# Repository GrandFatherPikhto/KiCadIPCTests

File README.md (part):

# KiCad IPC Test Framework

**General purpose of the project** – creating a unified, safe, and extensible system for testing and automating interaction with the **KiCad** PCB editor via IPC (the `kipy` library). The toolkit allows you to:

- perform **smoke, safe, and mutating tests** on a real board;
- conduct **static contract analysis** of the installed version of `kipy`;
- automate typical operations (moving, flipping components, creating vias);
- diagnose connection state and reproduce known KiCad bugs.

The project is built around a **single runner** that manages configuration, logging, the test registry, and the connection to KiCad, ensuring integrity and repeatability of runs.

---

## Installation and Dependencies

- **Python 3.8+**
- **KiCad 9 or 10** with GUI running (IPC works only with an open PCB editor)
- **`kipy` library** – official Python wrapper for KiCad IPC (installed separately, see [repository](https://gitlab.com/kicad/libraries/kipy))
- Optionally for CLI netlist export – **`kicad-cli`** (included in KiCad)

It is recommended to use a virtual environment:

```bash
python -m venv venv
source venv/bin/activate   # Windows: venv\Scripts\activate
pip install kipy
```

---

## Configuration

All settings are done via a **single YAML file**. Minimal structure:

```yaml
kicad:
  timeout_ms: 20000               # IPC call timeout (ms)

logging:
  console_level: INFO             # console log level
  file: logs/test.log             # log file path
  file_level: DEBUG               # file log level
  rotate_max_bytes: 5242880       # max size per file
  rotate_backups: 3               # number of rotations

boards:                           # parameter profiles for different boards
  10CL006:
    ref: "C5"                     # default refdes
    pad: "1"                      # pad number
    zone: "RA_DECAP_ZONE"         # zone name
    net: "GND"                    # net name
    extra:                        # additional parameters
      offset_mm: 1.2

suites:                           # test groups
  smoke:
    enabled: true
    tests:
      smoke_footprints:
        enabled: true
  mutating:
    enabled: false                # dangerous tests are disabled by default
    tests:
      mutating_flip_then_update_items:
        enabled: false
        dangerous: true
        params:
          ref: "Ctest"
```

Parameters from `boards` and `tests` are merged via `resolve_params` (test parameters have higher priority).

---

## Running

**Main command:**

```bash
python -m runner.run --config <config.yaml> [--board <profile>] [--suite <suite>] [--test <test>]
```

- `--config` – required, path to YAML config.
- `--board` – board profile name (substitutes `ref/pad/zone/net` parameters).
- `--suite` – run only the specified suite.
- `--test` – run a specific test (even if not described in config – it will execute with default parameters, **except dangerous ones** – they require explicit `enabled: true`).

**Examples:**

```bash
# All safe tests for board 10CL006
python -m runner.run --config config/10CL006.yaml --board 10CL006 --suite safe

# Single smoke test on component C5
python -m runner.run --config config/10CL006.yaml --board 10CL006 --test smoke_footprints

# Dangerous test (only if enabled in config)
python -m runner.run --config config/10CL006.yaml --test decap_create_one_via
```

After execution, the runner outputs a summary `[PASS]/[FAIL]` and an exit code: `0` – all passed, `1` – some errors, `2` – attempt to run a disabled dangerous test.

---

## Project Structure

```
project_root/
├── core_api/                     # Base abstraction layer over kipy
│   ├── board.py                  # Transactions, board metadata (size, layers)
│   ├── footprints.py             # Footprint search, read, modification, flip
│   ├── geometry.py               # MM constant, coordinate utilities
│   ├── kicad_client.py           # Connection, run_action, version
│   ├── nets.py                   # Nets (search by name, code map)
│   ├── pads.py                   # Pads (obtained via definition.items)
│   ├── project.py                # Project and schematic paths
│   ├── selection.py              # Description of selected items
│   ├── vias.py                   # Create/delete vias
│   ├── zones.py                  # Zones (search, outline points)
│   └── __init__.py
│
├── runner/                       # Unified launch system
│   ├── config_schema.py          # Dataclass models and YAML loading
│   ├── logging_setup.py          # Logging setup (console + rotating file)
│   ├── registry.py               # Test registry (@register decorator)
│   ├── run.py                    # Main script (parsing, discovery, execution)
│   ├── step_helper.py            # call_step – logging with timing
│   └── __init__.py
│
├── tests/
│   ├── decap_tools/              # Dangerous tests for capacitors and vias
│   │   ├── test_create_one_via.py      # Create/delete one via
│   │   ├── test_flip_one_cap.py        # Flip component (toggle)
│   │   ├── test_move_one_cap.py        # Shift component along X
│   │   ├── test_via_placer.py          # Automatic via placement with keepout
│   │   ├── geometry/
│   │   │   ├── boundary.py             # Ray–polygon intersection, normals
│   │   │   └── keepout.py              # Keepout zones, free point search
│   │   └── __init__.py
│   │
│   ├── mutating/                 # Regression dangerous tests
│   │   ├── test_flip_then_update_items.py      # Stale object after flip
│   │   ├── test_footprint_rotation_linkage.py  # Rotation and schematic link (#21655)
│   │   ├── test_pad_ownership_comparison.py    # Comparison of pad acquisition methods
│   │   ├── test_refill_zones_busy_repro.py     # Eternal busy reproduction
│   │   └── __init__.py
│   │
│   ├── safe/                    # Safe tests (read-only)
│   │   ├── test_board_info.py          # Board summary (get_info)
│   │   ├── test_cli_netlist.py         # Netlist export via kicad-cli
│   │   ├── test_connection_reuse.py    # Single connection reuse check
│   │   ├── test_footprints_probe.py    # Temporary busy diagnostics
│   │   ├── test_project.py             # Project and schematic paths
│   │   ├── cli_utils.py                # kicad-cli utilities (not a test)
│   │   └── __init__.py
│   │
│   ├── smoke/                   # Smoke tests for basic modules
│   │   ├── test_board.py               # commit_with_retry (empty transaction)
│   │   ├── test_footprints.py          # Footprint reading and bounding box
│   │   ├── test_kicad_client.py        # Version and board re-fetch
│   │   ├── test_nets.py                # Net search by name
│   │   ├── test_pads.py                # Footprint pad reading
│   │   ├── test_selection.py           # Selection description (no input)
│   │   ├── test_vias.py                # Create/delete via (no leftovers)
│   │   ├── test_zones.py               # Zone search and outline point
│   │   └── __init__.py
│   │
│   ├── static/                  # Static contract checks of kipy
│   │   ├── test_kipy_contract.py       # 12 API incompatibility checks
│   │   └── __init__.py
│   │
│   ├── toy/                     # Dummy tests for runner debugging
│   │   ├── dummy_tests.py              # dummy_ok, fail, raises, needs_params, dangerous
│   │   └── __init__.py
│   │
│   └── __init__.py
│
├── config/                      # (example) YAML configs for different boards
│   └── test_config.yaml
│
└── logs/                        # Log files (auto-created)
    └── test.log
```

---

## Important Notes

- **Dangerous tests** (flag `dangerous: true`) are **never run** without explicit `enabled: true` in the config – this protects against accidental board damage.
- **Single connection** – all tests in one run use the same connection, preventing socket leaks.
- **After GUI flip**, you must re‑read the board, otherwise local objects become stale.
- **Static tests** do not require KiCad running and can be executed in CI.

---

## Extending

To add a new test:

1. Create a Python file in one of the `tests/` subdirectories.
2. Define a function with signature `def run_test(logger, **params) -> bool`.
3. Register it with the `@register("unique_name", suite="my_suite", dangerous=False, needs_kicad=True)` decorator.
4. Describe the test in the YAML config (with parameters if needed).

The runner will automatically discover the test when the `tests` package is imported.

---

## License and Authorship

The project is developed for internal use and testing of KiCad IPC capabilities. All source code is distributed under a license compatible with KiCad (GPLv3).

# `runner` Module — Unified Test and Script Launch System

`runner` is a framework for organizing, configuring, and executing test scenarios that work with KiCad via IPC. It provides:

- **Single entry point** – script `run.py` with command‑line arguments.
- **Flexible configuration** via a YAML file, where tests can be enabled/disabled, parameters can be set for different boards, and dangerous tests can be marked.
- **Test registry** based on decorators – tests are automatically registered upon import.
- **Single KiCad connection** for the entire run, to avoid socket leaks and false `busy` errors.
- **Standardized logging** with console and rotating file output.
- **Error and exception handling** – a test is considered failed on any exception; the runner catches and logs it.
- **Protection against accidental dangerous test execution** – they run only with explicit `enabled: true` in the config, even if specified with `--test`.

---

## `runner` Module Structure

### 1. `config_schema.py` – data models and configuration loading

Defines dataclasses for all config levels:

- **`KicadConfig`** – IPC settings: `timeout_ms` (default 20000), `socket_path` (optional).
- **`LoggingConfig`** – log levels, file path, rotation.
- **`BoardProfile`** – named set of parameters for a specific board: `ref` (default component refdes), `pad` (pad number), `zone` (zone name), `net` (net name), plus `extra: Dict` for any additional parameters.
- **`TestEntry`** – description of one test: `name`, `enabled` (bool), `dangerous` (bool), `params` (override dictionary).
- **`SuiteConfig`** – group of tests: `name`, `enabled`, `tests: Dict[str, TestEntry]`.
- **`RootConfig`** – root node containing `kicad`, `logging`, `boards` (profiles dictionary), and `suites`.

Functions:
- `load_config(path)` → `RootConfig` – loads and parses YAML.
- `resolve_params(board_profile, test_entry)` → `Dict[str, Any]` – merges final parameters for a test: first the `ref/pad/zone/net` fields from the board profile, then `extra` from the profile, then `params` from the test entry (overriding on conflict).

---

### 2. `logging_setup.py` – logging setup

- `setup_logging(logger_name, console_level, file_path, file_level, rotate_max_bytes, rotate_backups)` → `Logger`.
- Creates two handlers: console (level `console_level`, usually `INFO`) and rotating file (level `file_level`, usually `DEBUG`).
- **Idempotent** – on repeated calls with the same logger name, old handlers are removed to avoid duplicates.
- Disables propagation to the root logger (`logger.propagate = False`).

---

### 3. `registry.py` – test registry

- Global dictionary `_REGISTRY: Dict[str, RegisteredTest]`.
- **`RegisteredTest`** – dataclass with fields: `name`, `suite`, `dangerous`, `needs_kicad`, `func`.
- Decorator **`@register(name, suite, dangerous=False, needs_kicad=False)`** registers a function. Checks uniqueness of the name.
- `needs_kicad=True` means the test requires `kicad` and `board` objects; the runner will pass them via parameters (from `SharedConnection`).
- Access functions:
  - `get(name)` – get a registered test.
  - `all_tests()` – all tests.
  - `tests_in_suite(suite)` – tests of a specific suite.
  - `clear()` – reset registry (for testing the runner itself).

---

### 4. `step_helper.py` – step‑by‑step logging with timing

- **`call_step(logger, label, fn, *args, **kwargs)`** → `(result, success)`.
- Calls `fn`, logs the label and execution time in milliseconds.
- On exception, logs the error and returns `(None, False)` – **does not throw**.
- Used in tests for detailed tracking of each API call, to know at which step an error occurred.

---

### 5. `run.py` – main entry point

**Main script** performing the following steps:

#### Command‑line argument parsing

- `--config` (required) – path to YAML config.
- `--board` (optional) – board profile name from config.
- `--suite` (optional) – run only one suite.
- `--test` (optional) – run only one test by name.

#### Initialization

1. Loads config (`load_config`).
2. Sets up logging via `setup_logging` with config parameters.
3. Performs **test discovery**: function `discover_tests(package_name="tests")` recursively imports all modules inside the `tests` package. This ensures all `@register` decorators fire and populate the registry.

#### Test selection

Function `select_tests(cfg, suite_name, test_name)` returns a list of `(suite_name, TestEntry)` to run, considering `enabled` and `dangerous`:

- If `--test` is specified:
  - Searches for the test in all config suites.
  - If found and `enabled: false` – raises `PermissionError` (protection).
  - If the test is not in the config – creates a temporary `TestEntry` with `enabled=True`, `dangerous=False`.
- If `--suite` is specified – takes only that suite (if enabled).
- Otherwise – all suites from the config.
- Inside a suite, iterates over all tests, checking `enabled` (and for dangerous ones – that `enabled` is explicitly `true`).

#### Connection management

Class **`SharedConnection`**:

- Lazily establishes a connection to KiCad via `kicad_client.connect()` on first access.
- Provides method `get()` → `(kicad, board)`.
- Method `refresh_board()` re‑reads the board (useful after GUI actions).
- Used for all tests with `needs_kicad=True` to open **one** connection for the entire run.

#### Test execution

For each selected test:

1. Gets the `RegisteredTest` from the registry by name.
2. Builds parameters via `resolve_params(board_profile, entry)`.
3. If `needs_kicad`, adds `kicad` and `board` from `SharedConnection`.
4. Logs the start (with `[DANGEROUS]` marker if applicable).
5. Calls the test function with parameters.
6. Catches any exceptions, logs them, and counts the test as failed.
7. Stores the result `(name, ok)`.

#### Final report

- Logs the total number of tests run.
- Prints each test with `[PASS]`/`[FAIL]`.
- Exits with code `0` (all passed) or `1` (at least one failed).
- Special code `2` – when `--test` points to a disabled test (protection).

---

## Running Utility Tests

### Requirements

- Installed **KiCad** (version 9 or 10) with GUI running (IPC works only with active PCB editor).
- Installed `kipy` library (see [official repository](https://gitlab.com/kicad/libraries/kipy)).
- Python 3.8+.

### Basic Command

```bash
python -m runner.run --config <path_to_config.yaml> [--board <board_name>] [--suite <suite_name>] [--test <test_name>]
```

Examples:

- Run all enabled tests of all suites (with profile `10CL006`):
  ```bash
  python -m runner.run --config config/test_config.yaml --board 10CL006
  ```

- Run only the `safe` suite:
  ```bash
  python -m runner.run --config config/test_config.yaml --board 10CL006 --suite safe
  ```

- Run one specific test (even if not enabled in the config, it will run with default parameters):
  ```bash
  python -m runner.run --config config/test_config.yaml --test dummy_ok
  ```

- Run a dangerous test (must be explicitly enabled in the config, otherwise rejected):
  ```bash
  python -m runner.run --config config/test_config.yaml --board 10CL006 --test decap_create_one_via
  ```

### Minimal YAML config structure

```yaml
kicad:
  timeout_ms: 20000

logging:
  console_level: INFO
  file: logs/test.log
  file_level: DEBUG
  rotate_max_bytes: 5242880
  rotate_backups: 3

boards:
  10CL006:
    ref: "C5"
    pad: "1"
    zone: "RA_DECAP_ZONE"
    net: "GND"
    extra:
      custom_param: value

suites:
  toy:
    enabled: true
    tests:
      dummy_ok:
        enabled: true
      dummy_fail:
        enabled: false

  mutating:
    enabled: false   # all mutating tests disabled by default
    tests:
      mutating_flip_then_update_items:
        enabled: false
        dangerous: true
        params:
          ref: "Ctest"
```

---

## Important Architectural Decisions

- **Safety by default** – dangerous tests (`dangerous: true`) do not run, even if `--test` is specified, unless `enabled: true` is set in the config. This protects against accidental board damage.
- **Single connection** – all tests in one run share the same connection, preventing `busy` errors and resource leaks.
- **Idempotent logging** – repeated calls to `setup_logging` do not create duplicate handlers.
- **Transparent error handling** – exceptions in tests do not abort the whole run; they are logged, and the runner continues with the remaining tests.

---

## Extending and Adding New Tests

1. Create a Python file in any subdirectory of `tests/` (e.g., `tests/my_suite/test_my_feature.py`).
2. Define a function with signature `def run_test(logger, **params) -> bool`.
3. Register it with the decorator:
   ```python
   from runner.registry import register

   @register("my_test", suite="my_suite", dangerous=False, needs_kicad=True)
   def run_test(logger, kicad, board, ref=None, **params):
       # test body
       return True
   ```
4. Describe the test in the YAML config (set `enabled`, `params` if needed).
5. Run with `--suite my_suite` or `--test my_test`.

---

# `core_api` — Base Layer for KiCad Interaction

`core_api` is a universal wrapper library over the official `kipy` (KiCad IPC) Python library. It provides a unified, type‑safe, and documented interface for working with an open board in KiCad’s PCB editor.

### Core Principles

- **No global state** – all functions take ready‑made `kicad` or `board` objects as explicit arguments. This makes the code easily testable, reusable, and safe in multi‑threading scenarios.
- **Transactional approach** – all board modifications are performed inside commits (`begin_commit` / `push_commit` / `drop_commit`). This ensures atomicity and allows rollback on error.
- **Working in millimetres** – all coordinates and sizes are accepted and returned in millimetres (`float`). The internal `kipy` representation uses nanometres (integers); conversion is performed automatically using the constant `MM = 1_000_000`.
- **Explicit cache refresh** – after operations that modify the board outside the standard `update_items` mechanism (e.g., after a GUI flip via `run_action`), local objects become stale. You should re‑read data via `board.get_footprints()` or `board.refresh()`.

---

## Module Structure

### 1. `geometry.py` – geometric constants and utilities

The most basic module, defining the coordinate conversion unit:

```python
MM = 1_000_000  # number of nanometres in one millimetre
```

Helper functions:

- `vec_mm(x_mm, y_mm)` → `Vector2` – creates a vector from millimetres.
- `to_mm(vector)` → `(x_mm, y_mm)` – converts a vector to millimetres.
- `bbox_size_mm(bbox)` → `(width_mm, height_mm)` – extracts dimensions from a `Box2` object.

All other modules rely on this module for consistent unit conversion.

---

### 2. `kicad_client.py` – connection and session management

Responsible for establishing a connection to a running KiCad instance and performing low‑level actions:

- `connect(timeout_ms=20000)` → `KiCad` – connects to the currently open project. Default timeout increased to 20 seconds (in `kipy` default is 2 seconds, insufficient for heavy transactions).
- `get_board(kicad)` → `Board` – returns the board object.
- `run_action(kicad, action)` – executes a GUI action (e.g., `"pcbnew.InteractiveEdit.flip"`). This is officially an unstable API (see `kipy` documentation), but necessary for operations not available via `update_items` (e.g., true component flip with mirroring).
- `get_version(kicad)` → `str` – returns the KiCad version (useful for diagnostics).

---

### 3. `board.py` – transactions, commits, and board metadata

The most important module for board modification. It provides:

- **Transaction management**:
  - `begin_commit(board)` – starts a transaction.
  - `push_commit(board, commit, description)` – commits changes.
  - `drop_commit(board, commit)` – rolls back a transaction.
  - `commit_with_retry(board, description, work_fn, retries=1)` – executes the passed function inside a transaction with automatic rollback on exception and one retry. Returns `bool` (success/failure) or throws if all attempts fail.

- **Cache refresh**:
  - `refresh(kicad)` → `Board` – re‑reads the board. **Must be called** after GUI actions (e.g., `flip_selected`) to obtain up‑to‑date local objects.

- **Board metadata**:
  - `get_edge_bounding_box_mm(board)` → `(width_mm, height_mm)` or `None` – dimensions from Edge.Cuts contour.
  - `get_copper_layer_count(board)` → `int` or `None` – number of copper layers.
  - `get_info(board)` → `dict` – combines all metadata into one dictionary.

**Important:** in `commit_with_retry`, the `commit` variable is initialised to `None` before the `try` block. This prevents `UnboundLocalError` if `begin_commit()` itself throws.

---

### 4. `footprints.py` – working with components

Module for searching, reading, and modifying footprints.

**Search:**
- `get_all(board)` → `list[FootprintInstance]` – all board components.
- `get_by_ref(board, ref)` → `FootprintInstance` or `None` – search by refdes (e.g., `"C5"`). Case‑sensitive.

**Reading:**
- `get_reference(fp)`, `get_value(fp)`, `get_footprint_name(fp)` – strings.
- `get_position_mm(fp)` → `(x_mm, y_mm)`.
- `get_angle_deg(fp)` → `float` (degrees).
- `get_layer(fp)` → `BoardLayer` (constant).
- `is_back(fp)` → `bool` – `True` if component is on the bottom side.
- `get_bounding_box_mm(board, fp)` → `(width_mm, height_mm)` or `None` – bounding box of a single component (excluding text).
- `get_bounding_boxes_mm(board, footprints)` → `list[Optional[tuple]]` – batch query for multiple footprints (more efficient than one‑by‑one).

**Modification (local, requires `update_items` inside a commit):**
- `set_position(fp, x_mm, y_mm)` – changes position in the local object.
- `set_angle_deg(fp, angle_deg)` – changes angle.

**True flip:**
- `flip_selected(kicad, board, footprints)` – performs a GUI flip for the given footprints. **After calling, you must re‑read the board** because local objects are stale.

---

### 5. `pads.py` – pads

Working with pads **in the context of an already known footprint**.

- `get_all(fp)` → `list[Pad]` – all pads of the footprint. Retrieved from `fp.definition.items` (without geometric search or extra API calls).
- `get_by_number(fp, number)` → `Pad` or `None` – search by number (e.g., `"1"`).
- `get_position_mm(pad)` → `(x_mm, y_mm)` – absolute position (kipy accounts for footprint rotation).
- `get_net_name(pad)` → `str` – net name or empty string if unconnected.
- `get_size_mm(pad)` → `(width_mm, height_mm)` or `None` – pad size (takes the first copper layer).
- `get_angle_deg(pad)` → `float` – padstack's own angle (already synchronised with footprint).

---

### 6. `nets.py` – nets

- `get_all(board)` → `list[Net]` – all nets.
- `get_by_name(board, name)` → `Net` or `None` – search by name.
- `build_net_map(board)` → `dict[int, str]` – dictionary `{code: name}`. **Note:** `Net.code` is marked deprecated in `kipy`, so use of this function is not recommended for production code; retained only for debugging.

---

### 7. `vias.py` – vias

- `make(position_mm, net, drill_mm=0.3, diameter_mm=0.6)` → `Via` – creates a `Via` object (not yet on the board). Then you need to call `board.create_items([via])` inside a transaction.
- `remove_by_id(board, uuid_str)` – removes an object by UUID. **Important:** internally uses `board.remove_items_by_id([KIID])`, where `KIID` is an object, not a string. The function correctly converts the string.

---

### 8. `zones.py` – zones (including Rule Areas)

- `get_by_name(board, name)` → `Zone` or `None` – search by name.
- `get_boundary_points(zone)` → `list[Vector2]` – outline points (only nodes of type `has_point`; arcs ignored). For most rectangular/polygonal zones this is sufficient.

---

### 9. `project.py` – project and schematic paths

- `get_project_path(board)` → `str` or `None` – project directory.
- `get_project_name(board)` → `str` or `None` – project name.
- `get_schematic_path(board)` → `str` or `None` – full path to `.kicad_sch` file (constructed from path and name).

---

### 10. `selection.py` – working with selection

Module for analysing the current selection in PCB editor.

- `get_selected_uuids(board)` → `set[str]` – UUIDs of all selected objects. **Critical:** for groups (`Group`), uses `group.proto.items` instead of the empty `group.items` (local cache).
- `get_selected_footprints(board)` → `list[FootprintInstance]` – only footprints from the selection (other types ignored).
- `describe_selected(board)` → `list[dict]` – detailed description of each selected component: refdes, position, angle, dimensions, list of pads with their nets and coordinates. Useful for diagnostics and debugging.

---

## Relationships and Typical Usage Scenario

1. **Connect** via `kicad_client.connect()`.
2. **Get board** via `kicad_client.get_board(kicad)`.
3. **Read** – use `footprints.get_by_ref`, `pads.get_all`, `nets.get_by_name`, etc.
4. **Modify** – always inside a transaction:
   ```python
   commit = board.begin_commit()
   try:
       # locally modify objects (set_position, set_angle, create via)
       board.update_items([modified_objects])
       board.create_items([new_via])
       board.push_commit(commit, "my change")
   except Exception:
       board.drop_commit(commit)
       raise
   ```
5. **After GUI actions** (e.g., `footprints.flip_selected`) always call `board = kicad_client.get_board(kicad)` or `board.refresh()` to update local objects.

---

## Safety and Performance Notes

- **Timeout** increased to 20 seconds – sufficient for bulk operations (hundreds of objects).
- **Batch requests** – use `get_bounding_boxes_mm` instead of looping `get_bounding_box_mm` to save time.
- **No geometric mapping** of pads to footprints – we always obtain pads via `definition.items` of a known footprint, which is more reliable and faster.
- **Dangerous operations** (flip, create/delete objects) are performed only in tests with the `dangerous` flag, but `core_api` itself does not contain protection logic – that is left to the runner.

---

# `tests/decap_tools` — Utilities and Tests for Decoupling Capacitors and Vias

The `tests/decap_tools/` directory contains **dangerous** diagnostic and helper tests designed to verify and demonstrate IPC interaction with KiCad for typical component operations (move, flip) and vias (create, delete, automatic placement). These tests are part of the overall runner system, registered in the `decap_tools` suite, and require explicit enabling (`enabled: true`) in the config because they modify the real board.

---

## Directory Structure

```
tests/decap_tools/
├── test_create_one_via.py
├── test_flip_one_cap.py
├── test_move_one_cap.py
├── test_via_placer.py
└── geometry/
    ├── boundary.py
    └── keepout.py
```

---

## 1. `test_create_one_via.py` – minimal via create/delete test

**Purpose:** testing basic `create_items()` and `remove_items_by_id()` operations on a single via. The test creates a via near the centre of the specified component, saves its UUID in a JSON file (`.last_test_via.json`) for later deletion without manual ID copying.

**Function:**  
`run_test(logger, kicad, board, ref=None, offset_mm=1.2, net="GND", drill_mm=0.3, diameter_mm=0.6, remove=False, remove_uuid=None, **params) -> bool`

- **Parameters:**
  - `ref` – component refdes (required if `remove=False`).
  - `offset_mm` – X offset from component centre (mm).
  - `net` – net name (default `"GND"`).
  - `drill_mm` and `diameter_mm` – via dimensions.
  - `remove` – if `True`, deletes a via instead of creating (using saved UUID or `remove_uuid`).
- **Logic:**
  - On deletion: if `remove_uuid` not given, reads `id` from JSON.
  - On creation: finds component, net, builds via, performs transaction `begin_commit` → `create_items` → `push_commit`, saves `id` to JSON.
- **Uses:** `core_api.footprints`, `core_api.nets`, `core_api.vias`, `core_api.board` (transactions), `runner.step_helper.call_step`.

---

## 2. `test_flip_one_cap.py` – component flip (toggle)

**Purpose:** testing the true component flip (GUI action `pcbnew.InteractiveEdit.flip`), which mirrors pads and silkscreen, unlike simple `.layer` change. Useful as a quick self‑check of flip functionality in the current KiCad version.

**Function:**  
`run_test(logger, kicad, board, ref=None, **params) -> bool`

- **Parameters:** `ref` – component refdes.
- **Logic:**
  - Logs component state before flip (layer, position, angle).
  - Calls `footprints.flip_selected(kicad, board, [target])`.
  - Re‑reads component and logs state after.
  - Returns `True` if layer changed to `BL_B_Cu` (or at least changed from original).
- **Important:** flip is a toggle; a second call will flip it back.
- **Uses:** `core_api.footprints` (specifically `flip_selected`).

---

## 3. `test_move_one_cap.py` – shift component along X axis

**Purpose:** isolated IPC write test – shifting one component by a given distance. Used to diagnose transaction hangs (`begin_commit`) and the `update_items` mechanism.

**Function:**  
`run_test(logger, kicad, board, ref=None, delta_mm=1.0, revert=False, **params) -> bool`

- **Parameters:** `ref` – component refdes; `delta_mm` – shift magnitude (mm); `revert` – if `True`, shift in opposite direction (`-delta_mm`).
- **Logic:**
  - Calculates new position.
  - Opens transaction, updates position via `update_items`, commits.
- **Uses:** `core_api.footprints` (read and modify position), `core_api.geometry.vec_mm`, `runner.step_helper.call_step`.

---

## 4. `test_via_placer.py` – automatic via placement near GND pads

**Purpose:** placing vias near GND pads of given components with three offset strategies (`center`, `edge`, `courtyard`), finding free space with keepout zones from other components and existing vias.

**Function:**  
`run_test(logger, kicad, board, gnd_net_name="GND", via=None, components=None, dry_run=False, **params) -> bool`

- **Parameters:**
  - `gnd_net_name` – net name (default `"GND"`).
  - `via` – dictionary of via parameters:
    - `offset_from` – `"center"`, `"edge"`, or `"courtyard"`.
    - `offset_mm` – base offset (mm).
    - `angle_deg` – preferred angle (if not given, computed automatically).
    - `drill_mm`, `diameter_mm` – via dimensions.
    - `keepout_clearance_mm` – margin for keepout zones.
    - `search_step_mm`, `search_max_radius_mm`, `search_n_directions` – free point search parameters.
  - `components` – list of dicts with fields `ref` (required), `offset_mm`, `angle_deg` (override global).
  - `dry_run` – if `True`, only logs, does not create vias.
- **Logic:**
  - For each component:
    - Finds footprint and GND pad.
    - Determines offset strategy.
    - Computes ideal via position considering pad rotation and Courtyard (if selected).
    - Builds keepout zones from bounding boxes of other components and all vias.
    - Searches for a free point near the ideal position respecting preferred direction.
    - Creates a via object.
  - Finally, executes a single transaction to create all vias (or nothing if `dry_run`).
- **Helper functions inside the file:**
  - `intersect_ray_with_rotated_rect` – ray‑rotated‑rectangle intersection (for `edge`).
  - `get_courtyard_polygon` – extracts Courtyard polygon points from `fp.definition.items` (fixed – now correctly handles `BoardRectangle` and `BoardPolygon`).
  - `compute_ideal_position` – computes ideal position based on chosen strategy.
- **Uses:** `core_api.footprints`, `core_api.pads`, `core_api.nets`, `core_api.vias`, `runner.step_helper.call_step`, local modules `geometry.boundary` and `geometry.keepout`.

---

## 5. `geometry/boundary.py` – polygon boundary utilities

**Purpose:** set of functions for working with polygons (Courtyard, zones) – computing ray‑polygon intersection, closest point on polygon, and outward normal. Used in `test_via_placer` for the `courtyard` strategy.

**Key functions:**
- `polyline_points(polyline)` – extracts points from a `PolyLine`.
- `_ray_segment_intersection(ox, oy, dx, dy, x1, y1, x2, y2)` – ray‑segment intersection.
- `ray_boundary_distance(center, target, boundary_pts)` – distance from `center` to the intersection of the ray with the polygon.
- `polygon_signed_area(polygon)` – signed area (to determine winding order).
- `closest_point_on_polygon(point, polygon)` – closest point on polygon and outward normal. **Fixed:** normal direction determined once for the entire polygon via signed area, which works correctly even in borderline cases where the point is just outside the polygon.

**Note:** code copied from the `KiCadDecapPlacer` project and is currently duplicated, but planned to be consolidated into a common location.

---

## 6. `geometry/keepout.py` – keepout zones and free point search

**Purpose:** building rectangular keepout zones from object bounding boxes and searching for a free point for via placement with a preferred direction.

**Class `Rect`:**
- Simple AABB rectangle in nanometres.
- Constructor from bounding box (`from_bbox`) with `clearance`.
- Circle approximation as square (`from_circle`).
- Intersection test (`intersects`).

**Functions:**
- `point_is_clear(point, via_radius, keepout)` – checks if the via circle of radius `via_radius` does not intersect any rectangle in `keepout`.
- `build_keepout(bboxes, clearance_mm, mm_per_unit)` – builds a list of `Rect` from a list of bounding boxes with margin.
- `find_free_point(ideal, keepout, via_radius, preferred_direction, step_mm, max_radius_mm, mm_per_unit, n_directions)` – searches for the closest free point to `ideal`, expanding in concentric rings. On each ring, checks the preferred direction first, then evenly spaced directions. Returns `Vector2` or `None` if no place found within `max_radius_mm`.

**Used in:** `test_via_placer` for final via positioning.

---

## Relationships and Dependencies

- All tests use **`core_api`** for accessing board objects and performing operations.
- **`test_via_placer`** heavily uses the geometry modules (`boundary`, `keepout`) and provides a fixed implementation for obtaining Courtyard.
- Tests are registered via **`runner.registry`** and use **`runner.step_helper.call_step`** for unified logging and error handling.
- **State saving** (`.last_test_via.json` in `test_create_one_via`) allows deleting created objects without manually entering a UUID.

---

## Running and Configuration

Tests from `decap_tools` are **disabled by default** (`enabled: false` in config) due to their dangerous nature. To run them, you must explicitly enable them in the YAML config, specifying required parameters (e.g., `ref`, `net`, `offset_mm`, etc.).

Example enabling a suite and a specific test:

```yaml
suites:
  decap_tools:
    enabled: true
    tests:
      decap_create_one_via:
        enabled: true
        params:
          ref: "C5"
          net: "GND"
          offset_mm: 1.2
```

Run:

```bash
python -m runner.run --config config.yaml --board 10CL006 --test decap_create_one_via
```

KiCad must be running with the board open, and the component `C5` must exist. For `test_via_placer`, a `components` list is required in the test parameters.

---

# `tests/mutating` — Regression Tests for Critical IPC Operations

The `tests/mutating/` directory contains **dangerous** tests that modify the real board and serve to:

- **Regression test** IPC calls related to object modifications (rotations, flip, positioning).
- **Reproduce known KiCad bugs**, for example:
  - flip rollback when using stale local objects;
  - possible break of symbol ↔ footprint link when rotating a footprint;
  - board "stuck" after asynchronous `refill_zones(block=False)` call.
- **Verify architectural decisions**, such as whether geometric mapping is needed to find pads.

All tests are registered in the `mutating` suite, use a shared connection (`needs_kicad=True`), and step‑by‑step logging via `call_step`. They are **disabled** (`enabled: false`) by default in the config – run deliberately only on test boards.

---

## 1. `test_flip_then_update_items.py` – regression on stale object after flip

**File:** `test_flip_then_update_items.py`  
**Test name:** `mutating_flip_then_update_items`

### Purpose
Checks that after a GUI flip (`pcbnew.InteractiveEdit.flip`), using the old local `Footprint` object in `update_items()` silently rolls back the layer change. The test demonstrates the **wrong** path (A) and the **correct** path (B) with re‑reading the footprint after the flip.

### Function
```python
run_test(logger, kicad, board, ref=None, **params) -> bool
```

**Parameters:** `ref` – refdes of the test component (required).

### Logic
1. Saves original layer and position.
2. **Variant A (wrong):**
   - Selects the component, executes `run_action("pcbnew.InteractiveEdit.flip")`.
   - Opens a transaction, modifies the **old** `target.position` (shift by 0.5 mm).
   - Calls `board.update_items([target])` – this rolls back the layer.
   - Checks if the layer returned to the original – if yes, bug reproduced.
3. **Variant B (correct):**
   - Calls `footprints.flip_selected(kicad, board, [after_a])` (also a GUI flip, but via wrapper).
   - **Re‑reads** the footprint (`get_by_ref`) – gets a fresh object.
   - Opens a transaction, restores the original position and commits.
   - Checks that the layer became the original (second flip reverted it).
4. Logs results.

### Important Notes
- The test **mutates** the component (flip + shift), but restores its original state at the end via variant B.
- Demonstrates a critical bug: `update_items` with a stale object after flip is a silent no‑op for the layer, but the position shift is applied.
- Requires a test component (not production).

---

## 2. `test_footprint_rotation_linkage.py` – bug #21655 (symbol ↔ footprint link break)

**File:** `test_footprint_rotation_linkage.py`  
**Test name:** `mutating_footprint_rotation_linkage`

### Purpose
Checks indirect signs of integrity of the link between schematic symbol and footprint after rotation via IPC. Direct check is impossible because IPC does not provide access to the schematic editor. The test compares snapshots before and after rotation: `reference`, `value`, footprint name, `net` on each pad.

### Function
```python
run_test(logger, kicad, board, ref=None, angle_deg=45.0, auto_revert=True, **params) -> bool
```

**Parameters:**
- `ref` – component refdes (required).
- `angle_deg` – rotation amount in degrees (default 45°).
- `auto_revert` – if `True` (default), the test restores the original angle after verification.

### Logic
1. Creates `_snapshot(fp)` – dictionary with `ref`, `value`, `footprint_name`, `pad_count`, `pads` (sorted list of `(number, net)`).
2. Rotates the component by `angle_deg` via `board.update_items` (inside transaction).
3. Re‑reads the footprint and takes a post‑snapshot.
4. Compares snapshots – if they are identical (except angle), the test considers the PCB‑side connectivity intact.
5. If `auto_revert=True`, performs a reverse rotation (`-angle_deg`).
6. Logs result.

### Important Notes
- The test does **not prove** the absence of bug #21655 on the schematic side, but shows that `net` on pads is not lost.
- By default, the board is **left unchanged** due to `auto_revert`.
- If `auto_revert=False`, the component remains rotated for manual check in Schematic Editor.

---

## 3. `test_pad_ownership_comparison.py` – comparison of two pad acquisition methods

**File:** `test_pad_ownership_comparison.py`  
**Test name:** `mutating_pad_ownership_comparison`  
**Dangerous:** `False` (read‑only)

### Purpose
Checks whether geometric mapping is needed to associate pads with footprints. The static test `static_pad_has_no_footprint_backreference` already confirmed that `board.get_pads()` does not provide a reverse reference. However, `core_api.pads` uses `fp.definition.items` – this test compares both approaches on a real board.

### Function
```python
run_test(logger, kicad, board, **params) -> bool
```

### Logic
1. **Path A:** calls `board.get_pads()` (flat list of all pads) and checks for an attribute pointing to the footprint (expected `False`).
2. **Path B:** takes the first 5 footprints, for each obtains pads via `fp.definition.items` and reads `net` for each pad (no geometry).
3. Checks that all pads gave a `net` – if yes, geometric mapping is not needed.

### Important Notes
- Test is **safe** (read‑only) but placed in the `mutating` suite due to theme.
- Confirms that when the footprint is known, geometry is not required.

---

## 4. `test_refill_zones_busy_repro.py` – reproduction of eternal busy after `refill_zones(block=False)`

**File:** `test_refill_zones_busy_repro.py`  
**Test name:** `mutating_refill_zones_busy_repro`  
**Dangerous:** **very high** – may lead to an unrecoverable board state requiring KiCad restart.

### Purpose
Tests the hypothesis that calling `board.refill_zones(block=False, max_poll_seconds=1)` leaves an unfinished asynchronous job that "locks" the board: all subsequent calls (`get_footprints`, `get_tracks`, etc.) return `busy` forever.

### Function
```python
run_test(logger, kicad, board, **params) -> bool
```

### Logic
1. **Step 1 (baseline):** calls `get_footprints`, `get_tracks`, `get_nets` – verifies everything works before the operation.
2. **Step 2:** executes `board.refill_zones(block=False, max_poll_seconds=1)` – **exactly as in the original incident**.
3. **Step 3 (immediately after):** repeats the content calls and logs whether they broke.
4. **Step 4 (retries):** makes up to 6 attempts with 5‑second pauses to see if the lock releases by itself.
5. Logs the result.

### Important Notes
- **Most dangerous test.** If the hypothesis is confirmed, the board remains in a "broken" state, and the **only way out** is a full restart of the KiCad application.
- Run **only** on a test board, not in the middle of an important session.
- The test does not run `refill_zones` with `block=True` because that would block the IPC connection for a long time and is not a reproduction of the original incident.

---

## General Characteristics of the `mutating` Suite

| Test | Dangerous | Restores | Purpose |
|------|-----------|----------|---------|
| `flip_then_update_items` | yes | yes (variant B) | regression on stale object |
| `footprint_rotation_linkage` | yes | yes (`auto_revert`) | #21655 check (indirect) |
| `pad_ownership_comparison` | no | – | comparison of pad acquisition methods |
| `refill_zones_busy_repro` | **very high** | **no** (requires KiCad restart) | reproduction of eternal busy |

### Running

All tests are disabled by default in the config. To run them, you must explicitly set `enabled: true` for the `mutating` suite and/or for the specific test, and provide required parameters (e.g., `ref` for the first three).

Example enabling:

```yaml
suites:
  mutating:
    enabled: true
    tests:
      mutating_flip_then_update_items:
        enabled: true
        params:
          ref: "Ctest"
      mutating_footprint_rotation_linkage:
        enabled: true
        params:
          ref: "Ctest"
          auto_revert: true
      mutating_refill_zones_busy_repro:
        enabled: true
```

Run:

```bash
python -m runner.run --config config.yaml --board 10CL006 --test mutating_flip_then_update_items
```

**Warning:** before running `mutating_refill_zones_busy_repro`, make sure you are prepared to restart KiCad and do not lose important changes.

---

# `tests/safe` — Safe Tests (Read‑Only)

The `tests/safe/` directory contains **safe** tests that **do not modify** the board and serve to:

- verify basic `core_api` functionality (reading board info, project, components);
- diagnose IPC connection state and busy situations;
- integrate with external tools (netlist export via `kicad-cli`).

All tests are registered in the `safe` suite, marked `dangerous=False`, use a shared KiCad connection (`needs_kicad=True`) and are **enabled by default** (`enabled: true`) in the config because they do not change the board.

---

## Directory Structure

```
tests/safe/
├── test_board_info.py
├── test_cli_netlist.py
├── test_connection_reuse.py
├── test_footprints_probe.py
├── test_project.py
└── cli_utils.py          # helper module (not a test)
```

---

## 1. `test_board_info.py` – board summary information

**Test name:** `safe_board_info`

### Purpose
Retrieves and logs general board information: number of footprints, nets, dimensions from Edge.Cuts, number of copper layers. Uses the new `core_api.board.get_info()`.

### Function
```python
run_test(logger, kicad, board, **params) -> bool
```

### Logic
- Calls `core_api.board.get_info(board)`.
- Logs the returned dictionary.
- Issues warnings if board is empty, size unknown, or layer count unknown.
- Always returns `True` (diagnostic test).

### Uses
- `core_api.board`

---

## 2. `test_cli_netlist.py` – netlist export via `kicad-cli`

**Test name:** `safe_cli_netlist`

### Purpose
Export netlist to XML format via external CLI tool `kicad-cli`, then parse the resulting file and output the number of nets and the first few nodes. This is a separate mechanism (subprocess), **not IPC**.

### Function
```python
run_test(logger, kicad, board, **params) -> bool
```

### Logic
1. Obtains schematic path via `core_api.project.get_schematic_path(board)`.
2. Creates a temporary XML file.
3. Calls `export_netlist(sch_path, tmp_path, logger)` (from `cli_utils.py`).
4. If successful, parses the XML via `parse_netlist_xml()`.
5. Logs the number of nets found and the first 5 nets with their nodes.
6. Deletes the temporary file.
7. Returns `True` if export and parsing succeeded.

### Uses
- `core_api.project`
- `cli_utils` (export and parse)

### Important Notes
- The test **takes noticeable time** (~19 seconds) due to the external process launch.
- `kicad-cli` must be installed and available on `PATH` or via the `KICAD_CLI_PATH` environment variable (see `cli_utils.find_kicad_cli`).

---

## 3. `test_connection_reuse.py` – connection reuse check

**Test name:** `safe_connection_reuse`

### Purpose
Regression test that the runner passes the **same** connection (`kicad` and `board`) to all tests, rather than opening a new one each time. This guarantees no socket leaks and no `busy` errors.

### Function
```python
run_test(logger, kicad, board, **params) -> bool
```

### Logic
- Calls `kicad_client.get_version(kicad)` 5 times and measures the time of each call.
- If all calls succeed and times are small (fractions of a millisecond), the test is considered successful.
- If each call opened a new connection, timings would be an order of magnitude higher (tens of ms).

### Uses
- `core_api.kicad_client`

### Important Notes
- The test does **not** inspect internal runner structures, but verifies behaviour from the user perspective (the objects passed).
- Passes if `get_version` consistently works on the passed connection.

---

## 4. `test_footprints_probe.py` – temporary busy diagnostics

**Test name:** `safe_footprints_probe`

### Purpose
Diagnostic test that attempts to call `board.get_footprints()` several times with pauses to check whether busy‑state releases by itself. **Does not fix** the issue, only records and logs.

### Function
```python
run_test(logger, kicad, board, **params) -> bool
```

### Logic
- Makes up to 6 attempts to call `board.get_footprints()` with 2‑second pauses.
- If at least one attempt succeeds, logs it and returns `True`.
- If all attempts returned busy, logs a warning and returns `True` (diagnostic test is not considered a failure).

### Uses
- `core_api.footprints` (via direct `board.get_footprints()` call)
- `runner.step_helper.call_step`

### Important Notes
- The test **is not considered a failure** even if busy persists – it is for analysis.
- Useful for detecting hangs caused by GUI tools or dialogs.

---

## 5. `test_project.py` – project and schematic paths

**Test name:** `safe_project`

### Purpose
Retrieves and logs the project directory, project name, and full path to the schematic file (`.kicad_sch`). Checks if the schematic file exists.

### Function
```python
run_test(logger, kicad, board, **params) -> bool
```

### Logic
- Calls `core_api.project.get_project_path(board)`, `get_project_name(board)`, `get_schematic_path(board)`.
- Logs all three values.
- Checks if the schematic file exists and issues a warning if not.
- Returns `True` if project path and name are not `None`.

### Uses
- `core_api.project`

---

## 6. `cli_utils.py` – helper utilities for `kicad-cli`

**This is not a test**, but a module with functions for working with the external CLI tool. Located in the `safe` directory because it is used only by `test_cli_netlist.py`.

### Functions

#### `find_kicad_cli(logger=None) -> str | None`
- Searches for `kicad-cli` executable:
  - via environment variable `KICAD_CLI_PATH`;
  - via standard KiCad installation paths (Windows);
  - via `shutil.which`.
- Returns the path or `None`.

#### `export_netlist(schematic_path, output_path, kicad_cli_path=None, logger=None) -> bool`
- Runs `kicad-cli sch export netlist --format kicadxml --output <output_path> <schematic_path>`.
- Returns `True` on success, `False` with logging on error.

#### `parse_netlist_xml(xml_path, logger=None) -> list[dict] | None`
- Parses the XML file generated by `kicad-cli`.
- Expects structure: root `<netlist>` → `<nets>` → many `<net name="...">` → `<node ref="..." pin="..."/>`.
- Returns a list of dicts `{"name": net_name, "nodes": [ref.pin, ...]}` or `None` on error.

---

## General Characteristics of the `safe` Suite

| Test | Dangerous | Execution time | Purpose |
|------|-----------|----------------|---------|
| `safe_board_info` | no | fast | board summary |
| `safe_cli_netlist` | no | ~19 s | netlist export via CLI |
| `safe_connection_reuse` | no | fast | connection reuse check |
| `safe_footprints_probe` | no | up to ~12 s | temporary busy diagnostics |
| `safe_project` | no | fast | project and schematic paths |

All tests use `needs_kicad=True` and receive `kicad` and `board` objects from the runner. They **do not modify** the board and are safe to run at any time.

### Running

The `safe` suite is enabled by default in the config (`enabled: true`). Run:

```bash
python -m runner.run --config config.yaml --board 10CL006 --suite safe
```

Or a single test:

```bash
python -m runner.run --config config.yaml --test safe_board_info
```

For `safe_cli_netlist`, `kicad-cli` must be installed and the schematic file must be accessible (via `core_api.project`).

---

# `tests/smoke` — Smoke Tests for Basic `core_api` Modules

The `tests/smoke/` directory contains **smoke tests** that verify the main `core_api` modules work and basic read/write operations execute without errors. These tests are **safe** (`dangerous=False`) and **do not leave changes** on the board (except `test_vias.py`, which creates and immediately deletes a test via). All tests use a shared KiCad connection (`needs_kicad=True`) and are registered in the `smoke` suite.

---

## Directory Structure

```
tests/smoke/
├── test_board.py
├── test_footprints.py
├── test_kicad_client.py
├── test_nets.py
├── test_pads.py
├── test_selection.py
├── test_vias.py
└── test_zones.py
```

---

## 1. `test_board.py` – transaction mechanism check

**Test name:** `smoke_board_commit`

### Purpose
Verifies basic `core_api.board.commit_with_retry` functionality with an empty transaction. Confirms the commit mechanism works without errors.

### Function
```python
run_test(logger, kicad, board, **params) -> bool
```

### Logic
- Calls `board.commit_with_retry(board, "smoke_board_commit: empty transaction", lambda: None)`.
- Logs the result (`True`/`False`).
- Returns the obtained value.

### Uses
- `core_api.board`

---

## 2. `test_footprints.py` – footprint reading

**Test name:** `smoke_footprints`

### Purpose
Verifies footprint reading: get all, search by `ref`, read position, angle, layer, size, and compare single vs batch bounding box query.

### Function
```python
run_test(logger, kicad, board, ref=None, **params) -> bool
```

**Parameters:** `ref` (optional) – component refdes; if not given, takes the first on the board.

### Logic
- Gets all footprints via `footprints.get_all(board)`.
- If board is empty – error.
- Determines target footprint: by `ref` or first.
- Reads and logs: `value`, `footprint_name`, position, angle, layer, `is_back`.
- Computes size via `get_bounding_box_mm` and `get_bounding_boxes_mm` (batch).
- Compares results – if different, test fails.
- Returns `True` if all operations succeed and sizes match.

### Uses
- `core_api.footprints`

---

## 3. `test_kicad_client.py` – connection and board retrieval

**Test name:** `smoke_kicad_client`

### Purpose
Checks that connection to KiCad is established and version/board can be obtained via `kicad_client`.

### Function
```python
run_test(logger, kicad, board, **params) -> bool
```

### Logic
- Calls `kicad_client.get_version(kicad)` – should return non‑empty string.
- Calls `kicad_client.get_board(kicad)` – should return a board object (not `None`).
- Returns `True` if both succeed.

### Uses
- `core_api.kicad_client`

---

## 4. `test_nets.py` – net reading

**Test name:** `smoke_nets`

### Purpose
Verifies getting all nets and searching for a specific one by name.

### Function
```python
run_test(logger, kicad, board, net="GND", **params) -> bool
```

**Parameters:** `net` – net name to search (default `"GND"`).

### Logic
- Gets all nets via `nets.get_all(board)`.
- If no nets – error.
- Searches for net by name via `nets.get_by_name(board, net)`.
- If not found – error.
- Logs the found net.
- Returns `True` if search succeeds.

### Uses
- `core_api.nets`

---

## 5. `test_pads.py` – pad reading

**Test name:** `smoke_pads`

### Purpose
Verifies obtaining pads of a footprint, search by number, read position, size, angle, and net.

### Function
```python
run_test(logger, kicad, board, ref=None, pad="1", **params) -> bool
```

**Parameters:**
- `ref` – component refdes (required).
- `pad` – pad number (default `"1"`).

### Logic
- Finds footprint by `ref` via `footprints.get_by_ref`.
- Gets all pads via `pads.get_all(fp)`.
- If no pads – error.
- Searches for pad by number via `pads.get_by_number(fp, pad)`. If not found, takes the first.
- Reads and logs: position, `net`, size, angle.
- Returns `True` if all succeed.

### Uses
- `core_api.footprints`, `core_api.pads`

---

## 6. `test_selection.py` – selection description

**Test name:** `smoke_selection`

### Purpose
Reads and describes the current selection in the PCB editor. Unlike the old version, it does **not block** user input, but simply reads the state.

### Function
```python
run_test(logger, kicad, board, **params) -> bool
```

### Logic
- Calls `selection.describe_selected(board)`.
- If nothing is selected – logs that and returns `True` (no selection is not an error).
- Otherwise, logs each selected component with its pads (position, size, nets).
- Returns `True`.

### Uses
- `core_api.selection`

---

## 7. `test_vias.py` – create and delete test via

**Test name:** `smoke_vias`

### Purpose
Verifies creating and deleting a via via `core_api.vias`. Creates a via near the specified component, then immediately deletes it – board remains clean.

### Function
```python
run_test(logger, kicad, board, ref=None, net="GND", **params) -> bool
```

**Parameters:**
- `ref` – component refdes (required).
- `net` – net for via (default `"GND"`).

### Logic
- Finds component by `ref`.
- Finds net by name.
- Computes via position (2 mm X offset from component centre).
- Creates via object via `vias.make`.
- Inside `commit_with_retry`:
  - calls `board.create_items([via])`, saves created `id`.
- If creation succeeds, inside a second transaction:
  - calls `vias.remove_by_id(board, created_id)`.
- Logs success or error.
- Returns `True` if both creation and deletion succeed.

### Uses
- `core_api.footprints`, `core_api.nets`, `core_api.vias`, `core_api.board` (commit_with_retry)

### Important Notes
- Test is **safe** because it always deletes the created via.
- If deletion fails, a warning about "leftover" on the board is logged.

---

## 8. `test_zones.py` – zone reading

**Test name:** `smoke_zones`

### Purpose
Finds a zone by name and reads its outline points.

### Function
```python
run_test(logger, kicad, board, zone=None, **params) -> bool
```

**Parameters:** `zone` – zone name (required, otherwise test is skipped).

### Logic
- If `zone` not passed – logs warning and returns `True` (skip).
- Searches for zone via `zones.get_by_name(board, zone)`.
- If not found – error.
- Gets outline points via `zones.get_boundary_points(z)`.
- Checks that there are at least 3 points.
- Returns `True` if zone found and outline valid.

### Uses
- `core_api.zones`

---

## General Characteristics of the `smoke` Suite

| Test | Dangerous | Parameters | Purpose |
|------|-----------|------------|---------|
| `smoke_board_commit` | no | – | transaction check |
| `smoke_footprints` | no | `ref` (opt.) | component and size reading |
| `smoke_kicad_client` | no | – | connection and version |
| `smoke_nets` | no | `net` (opt.) | net reading |
| `smoke_pads` | no | `ref` (req.), `pad` (opt.) | pad reading |
| `smoke_selection` | no | – | selection description |
| `smoke_vias` | no (create/delete) | `ref` (req.), `net` (opt.) | via create/delete |
| `smoke_zones` | no | `zone` (req.) | zone reading |

All tests use `needs_kicad=True` and receive `kicad` and `board` from the runner. They **do not leave changes** on the board (via is created and deleted). The `smoke` suite is enabled (`enabled: true`) by default in the config, as it is safe.

### Running

```bash
python -m runner.run --config config.yaml --board 10CL006 --suite smoke
```

Or a single test with required parameters (e.g., `ref` for `smoke_footprints`):

```bash
python -m runner.run --config config.yaml --test smoke_footprints
```

Parameters are substituted from the board profile in the config.

---

# `tests/static` — Static Contract Checks of the `kipy` Library

The `tests/static/` directory contains **one file** – `test_kipy_contract.py`, which implements **static contract tests**. These tests **do not require a running KiCad** and do not open an IPC connection – they analyse only types, attributes, method signatures, and object behaviour **directly during import** of the `kicad-python` (kipy) library. They serve for early detection of API incompatibilities that could lead to:

- **silent no‑op operations** (e.g., assigning to a copy of an object);
- **exceptions** (e.g., passing wrong type to a setter);
- **data loss** (e.g., ignoring rotation angle or component layer);
- use of **deprecated or unstable** APIs.

All tests are registered in the `static` suite, marked `dangerous=False`, **do not use** `needs_kicad` (default `False`), so the runner does not pass `kicad`/`board` objects. They run quickly and safely, ideal for CI/CD.

---

## File: `test_kipy_contract.py`

This file contains 12 separate checks, each emulating a specific bug found in `KiCadTemplateCloner` or `KiCadDecapPlacer` tools, or verifying documentation/behaviour of `kipy` against reality.

All checks use the `inspect` module for signature and docstring analysis, and create class instances to check for attributes/methods.

---

## List of Tests (Functions)

### 1. `static_via_drill_attribute_name`

**Test name:** `static_via_drill_attribute_name`

**Purpose:** Checks that a `Via` object has a flat attribute `drill_diameter`, not nested `drill.diameter` (as mistakenly used in `KiCadTemplateCloner`).

**Logic:**
- Creates a `Via` instance.
- Checks `hasattr(v, "drill")` (should be `False`) and `hasattr(v, "drill_diameter")` (should be `True`).
- Logs result.

**Bug source:** `extractor.py:99`, `applier.py:20` – accessing `via.drill.diameter`.

**Expected:** `has_flat_drill=True`, `has_nested_drill=False`.

---

### 2. `static_footprint_orientation_property_name`

**Test name:** `static_footprint_orientation_property_name`

**Purpose:** Checks that an `Angle` object has a property `degrees`, not a method `as_degrees()` (which was used in `extractor.py` and always returned `False`, losing the angle).

**Logic:**
- Creates `Angle.from_degrees(45.0)`.
- Checks `hasattr(a, "as_degrees")` (should be `False`) and `a.degrees == 45.0` (should be `True`).
- Logs result.

**Bug source:** `extractor.py:80` – `hasattr(fp.orientation, 'as_degrees')` always `False`, angle lost.

**Expected:** `has_method=False`, property `degrees` works.

---

### 3. `static_footprint_get_layer_method`

**Test name:** `static_footprint_get_layer_method`

**Purpose:** Checks that `FootprintInstance` has a property `layer`, not a method `get_layer()` (which was used in `extractor.py` and absent).

**Logic:**
- Creates `FootprintInstance()`.
- Checks `hasattr(fp, "get_layer")` (should be `False`) and `hasattr(fp, "layer")` (should be `True`).
- Logs result.

**Bug source:** `extractor.py:78` – calling `fp.get_layer()` leads to error or hardcoded `'F.Cu'`.

**Expected:** `has_method=False`, property `layer` exists.

---

### 4. `static_getter_returns_copy_not_reference`

**Test name:** `static_getter_returns_copy_not_reference`

**Purpose:** **Critical check** that getters like `.position` return a **copy** of the object, not a reference. Assigning to `.x` on that copy is a silent no‑op, the position does not change. This is the most important bug found in `applier.py`.

**Logic:**
- Creates `FootprintInstance`, sets `position = Vector2(1_000_000, 2_000_000)`.
- Saves `before_x = fp.position.x`.
- Executes `fp.position.x = 99_000_000` (as in `applier.py`).
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
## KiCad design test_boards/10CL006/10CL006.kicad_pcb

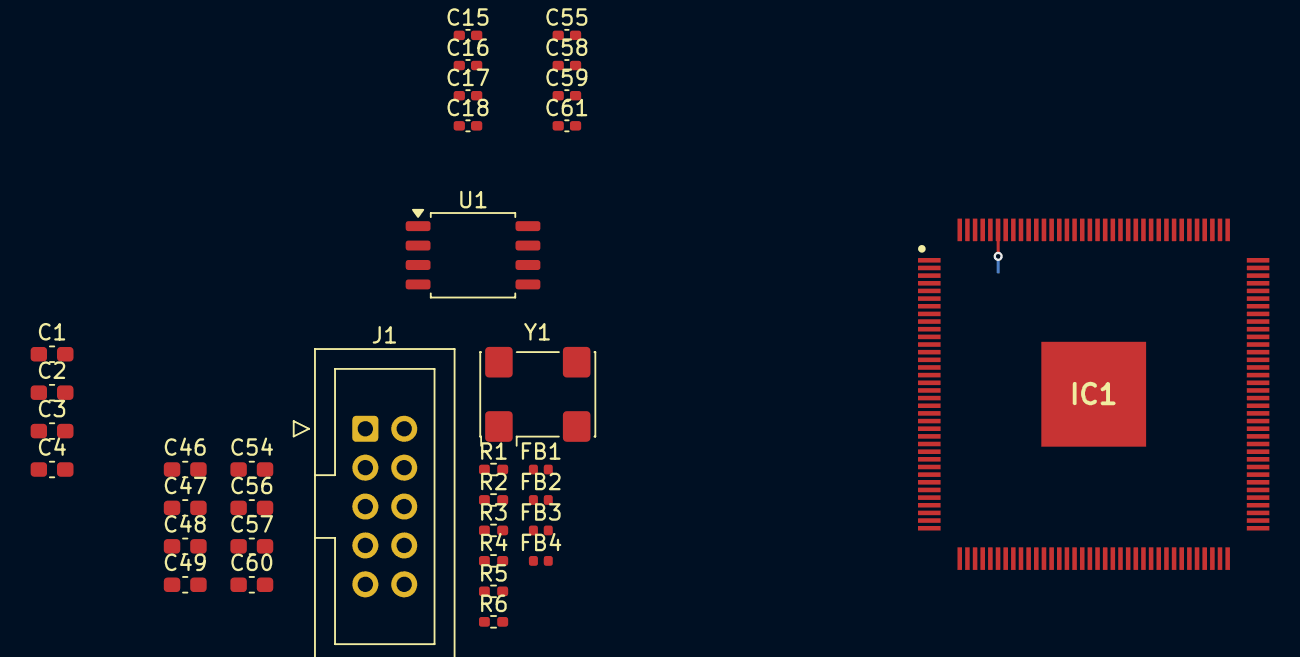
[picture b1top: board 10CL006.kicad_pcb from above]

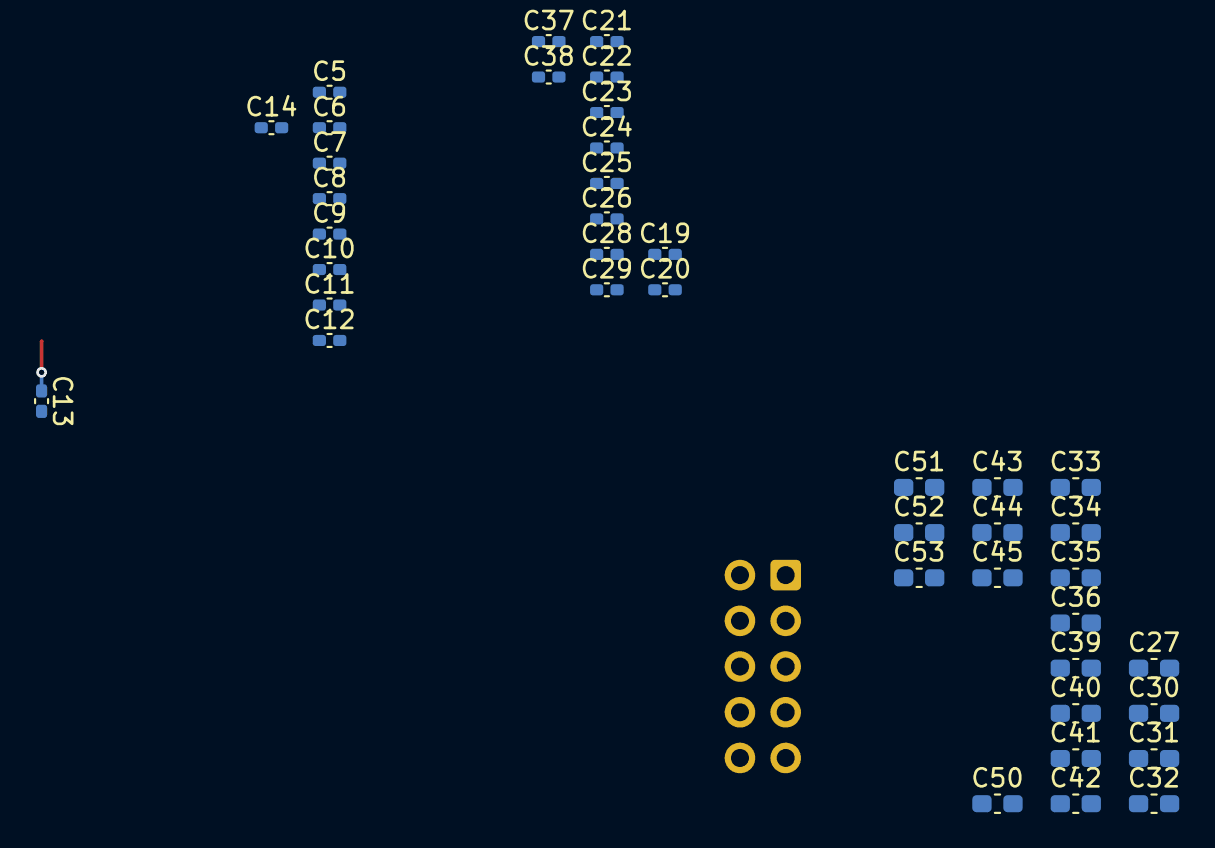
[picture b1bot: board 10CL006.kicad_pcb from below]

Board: 2 copper layers, 75 parts (41 on the bottom side), 23 nets.

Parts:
C1, C2, C3, C4, C46, C47, C48, C49, C54, C56, C57, C60: 1uF; C_0603_1608Metric_Pad1.08x0.95mm_HandSolder
C5, C6, C7, C8, C9, C10, C11, C12, C13, C14, C15, C16, C17, C18, C19, C20, C21, C22, C23, C24, C25, C26, C28, C29, C37, C38, C55, C58, C59, C61: 100 nF; C_0402_1005Metric_Pad0.74x0.62mm_HandSolder
C27, C30, C31, C32, C33, C34, C35, C36, C39, C40, C41, C42, C43, C44, C45, C50, C51, C52, C53: 4.7 uF; C_0603_1608Metric_Pad1.08x0.95mm_HandSolder
FB1, FB2, FB3, FB4: BLM15PD121SN1D; L_0402_1005Metric
IC1: 10CL006YE144C8G; QFP50P2200X2200X165-145N
J1: CL_JTAG; IDC-Header_2x05_P2.54mm_Vertical
R1: 1K; R_0402_1005Metric_Pad0.72x0.64mm_HandSolder
R2: 33; R_0402_1005Metric_Pad0.72x0.64mm_HandSolder
R3, R4, R5, R6: 2R2; R_0402_1005Metric_Pad0.72x0.64mm_HandSolder
U1: W25Q128JVS; SOIC-8_5.3x5.3mm_P1.27mm
Y1: SG-7050CAN; Oscillator_SMD_SeikoEpson_SG8002CA-4Pin_7.0x5.0mm

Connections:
+1V2: C1.1, C2.1, C15.1, C16.1, FB1.1, FB2.1
+1V2_VCCD_PLL: C37.1, C38.1, C47.1, C52.1, C53.1, FB2.2, IC1.37 (VCCD_PLL1), IC1.109 (VCCD_PLL2)
+1V2_VCCINT: C19.1, C20.1, C21.1, C22.1, C23.1, C24.1, C25.1, C26.1, C27.1, C39.1, C40.1, C41.1, C42.1, C43.1, C44.1, C45.1, C46.1, FB1.2, IC1.5 (VCCINT_1), IC1.29 (VCCINT_2), IC1.45 (VCCINT_3), IC1.61 (VCCINT_4), IC1.78 (VCCINT_5), IC1.102 (VCCINT_6), IC1.116 (VCCINT_7), IC1.134 (VCCINT_8)
+2V5: C3.1, C17.1, FB3.1
+2V5_VCCA: C28.1, C29.1, C48.1, C50.1, C51.1, FB3.2, IC1.35 (VCCA1), IC1.96 (MSEL1), IC1.107 (VCCA2)
+3V3: C4.1, C18.1, C54.1, C55.1, C57.1, C59.1, FB4.1, R4.1, R6.1
+3V3_FLASH: C60.1, C61.2, R3.2, R5.2, R6.2, U1.8 (VCC)
+3V3_OSCILL: C56.1, C58.2, R1.1, R4.2, Y1.4 (VCC)
+3V3_VCCIO: C5.1, C6.1, C7.1, C8.1, C9.1, C10.1, C11.1, C12.1, C13.1, C14.1, C30.1, C31.1, C32.1, C33.1, C34.1, C35.1, C36.1, C49.1, FB4.2, IC1.17 (VCCIO1), IC1.26 (VCCIO2), IC1.40 (VCCIO3_1), IC1.47 (VCCIO3_2), IC1.56 (VCCIO4_1), IC1.62 (VCCIO4_2), IC1.81 (VCCIO5), IC1.93 (VCCIO6), IC1.117 (VCCIO7_1), IC1.122 (VCCIO7_2), IC1.130 (VCCIO8_1), IC1.139 (VCCIO8_2), J1.4
/CL_ASDO: IC1.6 (IO_4), U1.5 (DI/IO_{0})
/CL_CLK_0: R2.1, Y1.3 (OUT)
/CL_CLK_0_IN: IC1.22 (CLK0), R2.2
/CL_CLK_ON: R1.2, Y1.1 (~ST)
/CL_DATA0: IC1.13 (IO_10), U1.2 (DO/IO_{1})
/CL_DCLK: IC1.12 (IO_9), U1.6 (CLK)
/CL_NCSO: IC1.8 (IO_6), U1.1 (~CS)
/CL_TCK: IC1.16 (TCK), J1.1
/CL_TDI: IC1.15 (TDI), J1.9
/CL_TDO: IC1.20 (TDO), J1.3
/CL_TMS: IC1.18 (TMS), J1.5
/FL_HOLD: R3.1, U1.7 (~HOLD/~RESET/IO_{3})
/FL_WP: R5.1, U1.3 (~WP/IO_{2})
GND: C1.2, C2.2, C3.2, C4.2, C5.2, C6.2, C7.2, C8.2, C9.2, C10.2, C11.2, C12.2, C13.2, C14.2, C15.2, C16.2, C17.2, C18.2, C19.2, C20.2, C21.2, C22.2, C23.2, C24.2, C25.2, C26.2, C27.2, C28.2, C29.2, C30.2, C31.2, C32.2, C33.2, C34.2, C35.2, C36.2, C37.2, C38.2, C39.2, C40.2, C41.2, C42.2, C43.2, C44.2, C45.2, C46.2, C47.2, C48.2, C49.2, C50.2, C51.2, C52.2, C53.2, C54.2, C55.2, C56.2, C57.2, C58.1, C59.2, C60.2, C61.1, IC1.4 (GND_1), IC1.19 (GND_2), IC1.21 (NCE), IC1.27 (GND_3), IC1.30 (GND_4), IC1.36 (GNDA1), IC1.41 (GND_5), IC1.48 (GND_6), IC1.57 (GND_7), IC1.63 (GND_8), IC1.64 (GND_9), IC1.79 (GND_10), IC1.82 (GND_11), IC1.94 (MSEL0), IC1.95 (GND_12), IC1.97 (MSEL2), IC1.104 (GND_13), IC1.108 (GNDA2), IC1.110 (GND_14), IC1.118 (GND_15), IC1.123 (GND_16), IC1.131 (GND_17), IC1.140 (GND_18), IC1.145 (EP_(GND)), J1.2, J1.10, U1.4 (GND), Y1.2 (GND)
